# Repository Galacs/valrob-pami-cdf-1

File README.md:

# Carte Pami CDF 1

Pami integrated circuit board with dual silent stepper driver and ToF sensor

## IC List

- ESP32-S3FH4R2 (Main MCU)
- LDL212 (MCU 3v3 LDO)
- BQ77905 (battery protection)
- WS2812B (RGB addressable led)
- MLT-5020 (buzzer)
- VL53L0X (ToF ranging sensor)
- 2x TMC2209 (Silent 3A stepper driver)

## Top preview

## Preview 3d render

## Pictures

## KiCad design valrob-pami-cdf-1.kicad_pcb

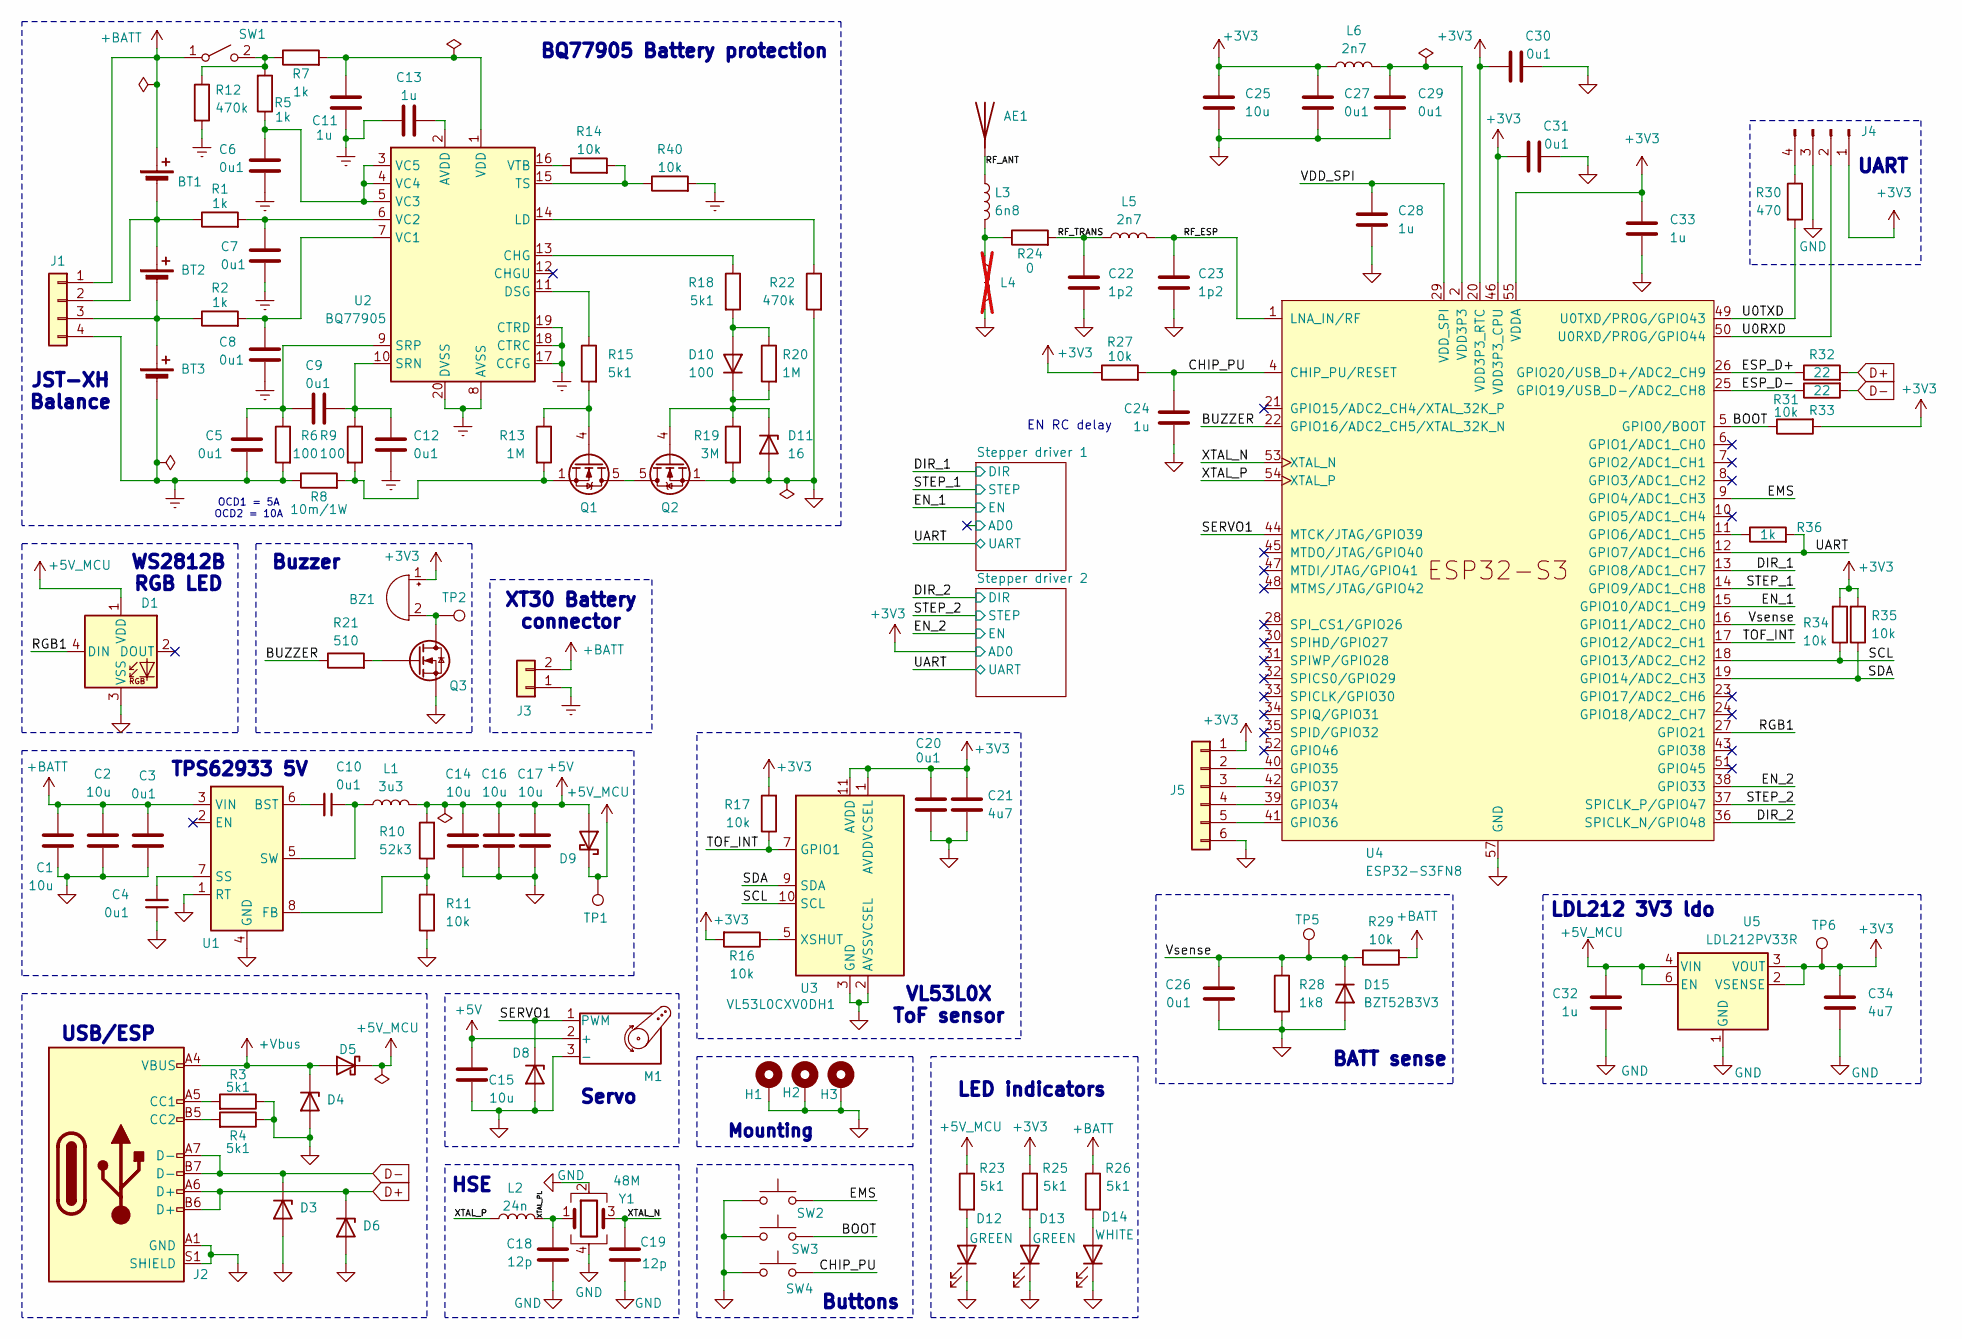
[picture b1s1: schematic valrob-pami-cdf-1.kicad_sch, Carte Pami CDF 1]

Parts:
AE1: Antenna; Johanson_2450AT18x100; Manufacturer Part Number RFANT3216120A5T; JLCPCB Part # C127629
BT1, BT2, BT3: Battery_Cell
BZ1: Buzzer; MagneticBuzzer_Huaneng_MLT-5020; Manufacturer Part Number MLT-5020; JLCPCB Part # C94598
C1, C2, C14, C15, C16, C17: 10u; C_0805_2012Metric; Manufacturer Part Number GRM21BR61H106KE43L; JLCPCB Part # C440198
C3, C4, C5, C6, C7, C8, C9, C10, C12, C20, C26, C27, C29, C30, C31: 0u1; C_0402_1005Metric; Manufacturer Part Number CL05B104KB54PNC; JLCPCB Part # C307331
C11, C13, C24, C28, C32, C33: 1u; C_0402_1005Metric; Manufacturer Part Number CL05A105KA5NQNC; JLCPCB Part # C52923
C18, C19: 12p; C_0402_1005Metric; Manufacturer Part Number 0402CG120J500NT; JLCPCB Part # C1547
C21, C34: 4u7; C_0402_1005Metric; Manufacturer Part Number CL05A475MP5NRNC; JLCPCB Part # C23733
C22, C23: 1p2; C_0402_1005Metric; Manufacturer Part Number GJM1555C1H1R2WB01D; JLCPCB Part # C76899
C25: 10u; C_0402_1005Metric; Manufacturer Part Number CL05A106MQ5NUNC; JLCPCB Part # C15525
D1: WS2812B; LED_WS2812B_PLCC4_5.0x5.0mm_P3.2mm; Manufacturer Part Number WS2812B-V5/W; JLCPCB Part # C2874885
D3, D4, D6, D8: H5VU10U; Diode_DFN1006; Manufacturer Part Number H5VU10U; JLCPCB Part # C22395519
D5, D9: D_Schottky; D_SMA; Manufacturer Part Number SS54; JLCPCB Part # C22452
D10: 100; D_SOD-323; Manufacturer Part Number 1N4148WS; JLCPCB Part # C2128
D11: 16; D_SOD-123; Manufacturer Part Number MMSZ5246B; JLCPCB Part # C19077429
D12, D13: GREEN; LED_0805_2012Metric; Manufacturer Part Number KT-0805G; JLCPCB Part # C2297
D14: WHITE; LED_0603_1608Metric; Manufacturer Part Number KT-0603W; JLCPCB Part # C2290
D15: BZT52B3V3; D_SOD-123; Manufacturer Part Number BZT52B3V3; JLCPCB Part # C19077392
H1, H2, H3: MountingHole_Pad; MountingHole_2.2mm_M2_Pad_Via
J1: Conn_01x04; JST_XH_S4B-XH-A_1x04_P2.50mm_Horizontal
J2: USB_C_Receptacle_USB2.0_14P; USB_C_Receptacle_HRO_TYPE-C-31-M-12; Manufacturer Part Number TYPE-C16PIN; JLCPCB Part # C393939
J3: Conn_01x02; AMASS_XT30PW-M_1x02_P2.50mm_Horizontal; Manufacturer Part Number XT30PW-M30.G.Y; JLCPCB Part # C431092
J4: Conn_01x04_Pin; PinHeader_1x04_P2.54mm_Vertical
J5: Conn_01x06; PinHeader_2x03_P2.54mm_Vertical
L1: 3u3; L_Sunlord_MWSA0402S; Manufacturer Part Number FXL0420-3R3-M; JLCPCB Part # C167207
L2: 24n; L_0402_1005Metric; Manufacturer Part Number LQW15AN24NG00D; JLCPCB Part # C167472
L3: 6n8; L_0402_1005Metric; Manufacturer Part Number LQG15HS6N8J02D; JLCPCB Part # C77110
L4: L; L_0402_1005Metric; not fitted
L5, L6: 2n7; L_0402_1005Metric; Manufacturer Part Number LQG15HS2N7S02D; JLCPCB Part # C77108
M1: Motor_Servo; PinHeader_1x03_P2.54mm_Horizontal
Q1, Q2: Q_NMOS; Vishay_PowerPAK_1212-8_Single; Manufacturer Part Number SIS412DN-T1-GE3; JLCPCB Part # C111309
Q3: Q_NMOS; SOT-323_SC-70; Manufacturer Part Number BSS138W; JLCPCB Part # C28646265
R1, R2, R5, R7, R36: 1k; R_0402_1005Metric; Manufacturer Part Number 0402WGF1001TCE; JLCPCB Part # C11702
R3, R4, R15, R18, R23, R25, R26: 5k1; R_0402_1005Metric; Manufacturer Part Number 0402WGF5101TCE; JLCPCB Part # C25905
R6, R9: 100; R_0402_1005Metric; Manufacturer Part Number 0402WGF1000TCE; JLCPCB Part # C25076
R8: 10m/1W; R_1206_3216Metric; Manufacturer Part Number FMF06FTHR010-LH; JLCPCB Part # C105362
R10: 52k3; R_0402_1005Metric; Manufacturer Part Number 0402WGF5232TCE; JLCPCB Part # C26982
R11, R14, R16, R17, R27, R29, R31, R34, R35, R40: 10k; R_0402_1005Metric; Manufacturer Part Number 0402WGF1002TCE; JLCPCB Part # C25744
R12, R22: 470k; R_0603_1608Metric; Manufacturer Part Number 0603WAF4703T5E; JLCPCB Part # C23178
R13, R20: 1M; R_0402_1005Metric; Manufacturer Part Number 0402WGF1004TCE; JLCPCB Part # C26083
R19: 3M; R_0603_1608Metric; Manufacturer Part Number 0603WAF3004T5E; JLCPCB Part # C23156
R21: 510; R_0402_1005Metric; Manufacturer Part Number 0402WGF5100TCE; JLCPCB Part # C25123
R24: 0; R_0402_1005Metric; Manufacturer Part Number 0402WGF0000TCE; JLCPCB Part # C17168
R28: 1k8; R_0603_1608Metric; Manufacturer Part Number 0603WAF1801T5E; JLCPCB Part # C4177
R30: 470; R_0402_1005Metric; Manufacturer Part Number 0402WGF4700TCE; JLCPCB Part # C25117
R32, R33: 22; R_0402_1005Metric; Manufacturer Part Number 0402WGF220JTCE; JLCPCB Part # C25092
SW1: SW_SPST; PinHeader_1x02_P2.54mm_Vertical
SW2: SW_Push; JST_XH_B2B-XH-A_1x02_P2.50mm_Vertical; Manufacturer Part Number B2B-XH-A(LF)(SN); JLCPCB Part # C158012
SW3, SW4: SW_Push; SW_SPST_TS-1088-xR020; Manufacturer Part Number TS-1088-AR02016; JLCPCB Part # C720477
TP1, TP2, TP5, TP6: TestPoint; TestPoint_Pad_D2.0mm
U1: TPS62933; SOT-583-8; Manufacturer Part Number TPS62933DRLR; JLCPCB Part # C3200405
U2: BQ77905; TSSOP-20_4.4x6.5mm_P0.65mm; Manufacturer Part Number BQ7790509PWR; JLCPCB Part # C2866527
U3: VL53L0CXV0DH1; ST_VL53L1x; Manufacturer Part Number VL53L0CXV0DH/1; JLCPCB Part # C91199
U4: ESP32-S3FN8; QFN-56-1EP_7x7mm_P0.4mm_EP4x4mm_ThermalVias; Manufacturer Part Number ESP32-S3FH4R2; JLCPCB Part # C3013940
U5: LDL212PV33R; DFN-6-1EP_2x2mm_P0.5mm_ST; Manufacturer Part Number LDL212PV33R; JLCPCB Part # C2969892
Y1: 48M; Crystal_SMD_2016-4Pin_2.0x1.6mm; Manufacturer Part Number R940000096; JLCPCB Part # C7206306

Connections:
+3V3: BZ1.1 (+), C20.1, C21.1, C25.1, C27.1, C30.1, C31.1, C33.1, C34.1, J4.1, J5.1, L6.1, R16.2, R17.2, R25.1, R27.1, R31.2, R34.2, R35.2, TP6.1 (1_1), U3.1 (AVDDVCSEL), U3.11 (AVDD), U4.20 (VDD3P3_RTC), U4.46 (VDD3P3_CPU), U4.55 (VDDA), U4.56 (VDDA), U5.2 (VSENSE), U5.3 (VOUT); also elsewhere on the board
+5V: C14.1, C15.1, C16.1, C17.1, D9.2 (A), L1.2, M1.2 (+), R10.2
+5V_MCU: C32.1, D1.1 (VDD), D5.1 (K), D9.1 (K), R23.1, TP1.1 (1_1), U5.4 (VIN), U5.6 (EN)
+BATT: BT1.1 (+), C1.1, C2.1, C3.1, J1.1, J3.2, R26.1, R29.2, SW1.1 (A), U1.3 (VIN); also elsewhere on the board
+Vbus: D4.1 (K), D5.2 (A), J2.A4 (VBUS), J2.A9 (VBUS), J2.B4 (VBUS), J2.B9 (VBUS)
/BOOT: R31.1, SW3.2, U4.5 (GPIO0/BOOT)
/BUZZER: R21.1, U4.22 (GPIO16/ADC2_CH5/XTAL_32K_N)
/CHIP_PU: C24.1, R27.2, SW4.2, U4.4 (CHIP_PU/RESET)
/DIR_1: U4.13 (GPIO8/ADC1_CH7); also elsewhere on the board
/DIR_2: U4.36 (SPICLK_N/GPIO48); also elsewhere on the board
/EMS: SW2.2, U4.9 (GPIO4/ADC1_CH3)
/EN_1: U4.15 (GPIO10/ADC1_CH9); also elsewhere on the board
/EN_2: U4.38 (GPIO33); also elsewhere on the board
/ESP_D+: R32.1, U4.26 (GPIO20/USB_D+/ADC2_CH9)
/ESP_D-: R33.1, U4.25 (GPIO19/USB_D-/ADC2_CH8)
/RF_ANT: AE1.1 (A_1), L3.1
/RF_ESP: C23.1, L5.2, U4.1 (LNA_IN/RF)
/RF_TRANS: C22.1, L5.1, R24.2
/RGB1: D1.4 (DIN), U4.27 (GPIO21)
/SCL: R34.1, U3.10 (SCL), U4.18 (GPIO13/ADC2_CH2)
/SDA: R35.1, U3.9 (SDA), U4.19 (GPIO14/ADC2_CH3)
/SERVO1: D8.1 (K), M1.1 (PWM), U4.44 (MTCK/JTAG/GPIO39)
/STEP_1: U4.14 (GPIO9/ADC1_CH8); also elsewhere on the board
/STEP_2: U4.37 (SPICLK_P/GPIO47); also elsewhere on the board
/TOF_INT: R17.1, U3.7 (GPIO1), U4.17 (GPIO12/ADC2_CH1)
/U0RXD: J4.2, U4.50 (U0RXD/PROG/GPIO44)
/U0TXD: R30.2, U4.49 (U0TXD/PROG/GPIO43)
/UART: R36.2, U4.12 (GPIO7/ADC1_CH6); also elsewhere on the board
/VDD_SPI: C28.1, U4.29 (VDD_SPI)
/Vsense: C26.1, D15.1 (K), R28.1, R29.1, TP5.1 (1_1), U4.16 (GPIO11/ADC2_CH0)
/XTAL_N: C19.1, U4.53 (XTAL_N), Y1.3
/XTAL_P: L2.1, U4.54 (XTAL_P)
/XTAL_PL: C18.2, L2.2, Y1.1
BGND: BT3.2 (-), C5.2, C6.2, C7.2, C8.2, C11.1, C12.2, C13.2, J1.4, J3.1, R6.2, R8.1, R12.2, R40.2, U2.8 (AVSS), U2.17 (CCFG), U2.18 (CTRC), U2.19 (CTRD), U2.20 (DVSS)
D+: D6.1 (K), J2.A6 (D+), J2.B6 (D+), R32.2
D-: D3.1 (K), J2.A7 (D-), J2.B7 (D-), R33.2
GND: C1.2, C2.2, C3.2, C4.1, C14.2, C15.2, C16.2, C17.2, C18.1, C19.2, C20.2, C21.2, C22.2, C23.2, C24.2, C25.2, C26.2, C27.2, C28.2, C29.2, C30.2, C31.2, C32.2, C33.2, C34.2, D1.3 (VSS), D3.2 (A), D4.2 (A), D6.2 (A), D8.2 (A), D11.2 (A), D12.1 (K), D13.1 (K), D14.1 (K), D15.2 (A), H1.1 (1_1), H2.1 (1_1), H3.1 (1_1), J2.A1 (GND), J2.A12 (GND), J2.B1 (GND), J2.B12 (GND), J2.S1 (SHIELD), J4.3, J5.6, L4.2, M1.3 (-), Q2.1 (S), Q2.2 (S), Q2.3 (S), Q3.2 (S), R3.1, R4.1, R11.1, R19.2, R22.2, R28.2, SW2.1, SW3.1, SW4.1, U1.1 (RT), U1.4 (GND), U3.2 (AVSSVCSEL), U3.3 (GND), U3.4 (GND), U3.6 (GND), U3.12 (GND), U4.57 (GND), U5.1 (GND), Y1.2, Y1.4; also elsewhere on the board
unnamed: BZ1.2 (-), Q3.3 (D), TP2.1 (1_1)
unnamed: D10.2 (A), R18.2, R20.1
unnamed: D10.1 (K), D11.1 (K), Q2.4 (G), R19.1, R20.2
unnamed: D12.2 (A), R23.2
unnamed: D13.2 (A), R25.2
unnamed: D14.2 (A), R26.2
unnamed: BT1.2 (-), BT2.1 (+), J1.2, R1.1
unnamed: BT2.2 (-), BT3.1 (+), J1.3, R2.1
unnamed: J2.A5 (CC1), R3.2
unnamed: J2.B5 (CC2), R4.2
unnamed: J4.4, R30.1
unnamed: J5.2, U4.40 (GPIO35)
unnamed: J5.3, U4.42 (GPIO37)
unnamed: J5.4, U4.39 (GPIO34)
unnamed: J5.5, U4.41 (GPIO36)
unnamed: L3.2, L4.1, R24.1
unnamed: Q1.5 (D), Q2.5 (D)
unnamed: Q1.4 (G), R13.1, R15.2
unnamed: Q1.1 (S), Q1.2 (S), Q1.3 (S), R8.2, R9.2, R13.2
unnamed: Q3.1 (G), R21.2
unnamed: R5.2, R7.1, R12.1, SW1.2 (B)
unnamed: C10.2, U1.6 (BST)
unnamed: R10.1, R11.2, U1.8 (FB)
unnamed: C4.2, U1.7 (SS)
unnamed: C10.1, L1.1, U1.5 (SW)
unnamed: C13.1, U2.2 (AVDD)
unnamed: R18.1, U2.13 (CHG)
unnamed: R15.1, U2.11 (DSG)
unnamed: R22.1, U2.14 (LD)
unnamed: C9.1, C12.1, R9.1, U2.10 (SRN)
unnamed: C5.1, C9.2, R6.1, U2.9 (SRP)
unnamed: R14.2, R40.1, U2.15 (TS)
unnamed: C8.1, R2.2, U2.7 (VC1)
unnamed: C7.1, R1.2, U2.6 (VC2)
unnamed: C6.1, R5.1, U2.3 (VC5), U2.4 (VC4), U2.5 (VC3)
unnamed: C11.2, R7.2, U2.1 (VDD)
unnamed: R14.1, U2.16 (VTB)
unnamed: R16.1, U3.5 (XSHUT)
unnamed: R36.1, U4.11 (GPIO6/ADC1_CH5)
VDD3P3: C29.1, L6.2, U4.2 (VDD3P3), U4.3 (VDD3P3)

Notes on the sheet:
UART
Buttons
LDL212 3V3 ldo
OCD1 = 5A OCD2 = 10A
JST-XH Balance
BQ77905 Battery protection
Servo
VL53L0X ToF sensor
EN RC delay
BATT sense
WS2812B RGB LED
LED indicators
Buzzer
TPS62933 5V
HSE
USB/ESP
XT30 Battery connector
Mounting

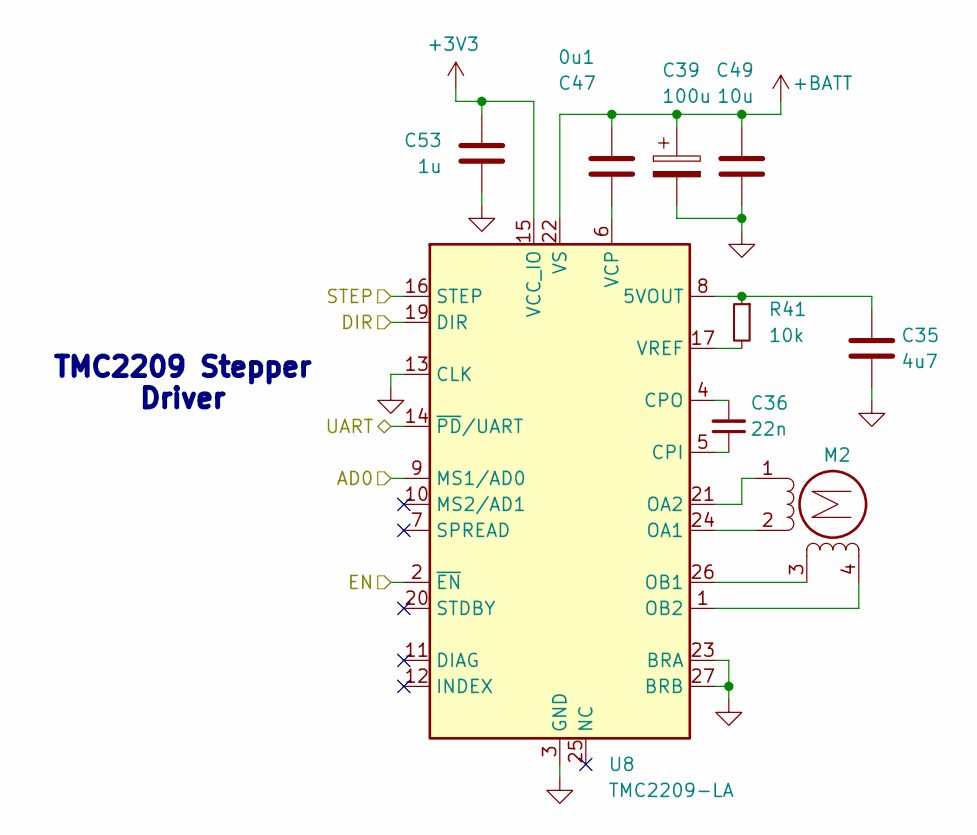
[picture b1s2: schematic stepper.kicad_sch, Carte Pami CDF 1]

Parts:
C35: 4u7; C_0402_1005Metric; Manufacturer Part Number CL05A475MP5NRNC; JLCPCB Part # C23733
C36: 22n; C_0402_1005Metric; Manufacturer Part Number 0402B223K500NT; JLCPCB Part # C1532
C39: 100u; CP_Elec_6.3x7.7; Manufacturer Part Number EEEFTH101XAP; JLCPCB Part # C165974
C47: 0u1; C_0402_1005Metric; Manufacturer Part Number CL05B104KB54PNC; JLCPCB Part # C307331
C49: 10u; C_0805_2012Metric; Manufacturer Part Number GRM21BR61H106KE43L; JLCPCB Part # C440198
C53: 1u; C_0402_1005Metric; Manufacturer Part Number CL05A105KA5NQNC; JLCPCB Part # C52923
M2: Stepper_Motor_bipolar; JST_XH_S4B-XH-A_1x04_P2.50mm_Horizontal
R41: 10k; R_0402_1005Metric; Manufacturer Part Number 0402WGF1002TCE; JLCPCB Part # C25744
U8: TMC2209-LA; VQFN-28-1EP_5x5mm_P0.5mm_EP3.7x3.7mm_ThermalVias; Manufacturer Part Number TMC2209-LA-T; JLCPCB Part # C2150710

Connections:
+3V3: C53.1, U8.15 (VCC_IO); also elsewhere on the board
+BATT: C39.1, C47.1, C49.1, U8.22 (VS), U8.28 (VS); also elsewhere on the board
/DIR_1: U8.19 (DIR); also elsewhere on the board
/EN_1: U8.2 (~EN); also elsewhere on the board
/STEP_1: U8.16 (STEP); also elsewhere on the board
/Stepper driver 1/AD0: U8.9 (MS1/AD0)
/UART: U8.14 (~PD/UART); also elsewhere on the board
GND: C35.2, C39.2, C49.2, C53.2, U8.3 (GND), U8.13 (CLK), U8.18 (GND), U8.23 (BRA), U8.27 (BRB), U8.29 (GND); also elsewhere on the board
unnamed: M2.1 (-_1), U8.21 (OA2)
unnamed: C35.1, R41.1, U8.8 (5VOUT)
unnamed: C36.1, U8.5 (CPI)
unnamed: C36.2, U8.4 (CPO)
unnamed: M2.2, U8.24 (OA1)
unnamed: M2.3, U8.26 (OB1)
unnamed: M2.4, U8.1 (OB2)
unnamed: C47.2, U8.6 (VCP)
unnamed: R41.2, U8.17 (VREF)

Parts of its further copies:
C37: 4u7; C_0402_1005Metric; Manufacturer Part Number CL05A475MP5NRNC; JLCPCB Part # C23733
C42: 22n; C_0402_1005Metric; Manufacturer Part Number 0402B223K500NT; JLCPCB Part # C1532
C45: 100u; CP_Elec_6.3x7.7; Manufacturer Part Number EEEFTH101XAP; JLCPCB Part # C165974
C48: 0u1; C_0402_1005Metric; Manufacturer Part Number CL05B104KB54PNC; JLCPCB Part # C307331
C50: 10u; C_0805_2012Metric; Manufacturer Part Number GRM21BR61H106KE43L; JLCPCB Part # C440198
C54: 1u; C_0402_1005Metric; Manufacturer Part Number CL05A105KA5NQNC; JLCPCB Part # C52923
M3: Stepper_Motor_bipolar; JST_XH_S4B-XH-A_1x04_P2.50mm_Horizontal
R42: 10k; R_0402_1005Metric; Manufacturer Part Number 0402WGF1002TCE; JLCPCB Part # C25744
U9: TMC2209-LA; VQFN-28-1EP_5x5mm_P0.5mm_EP3.7x3.7mm_ThermalVias; Manufacturer Part Number TMC2209-LA-T; JLCPCB Part # C2150710

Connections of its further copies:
+3V3: C54.1, U9.9 (MS1/AD0), U9.15 (VCC_IO); also elsewhere on the board
+BATT: C45.1, C48.1, C50.1, U9.22 (VS), U9.28 (VS); also elsewhere on the board
/DIR_2: U9.19 (DIR); also elsewhere on the board
/EN_2: U9.2 (~EN); also elsewhere on the board
/STEP_2: U9.16 (STEP); also elsewhere on the board
/UART: U9.14 (~PD/UART); also elsewhere on the board
GND: C37.2, C45.2, C50.2, C54.2, U9.3 (GND), U9.13 (CLK), U9.18 (GND), U9.23 (BRA), U9.27 (BRB), U9.29 (GND); also elsewhere on the board
unnamed: M3.1 (-_1), U9.21 (OA2)
unnamed: C37.1, R42.1, U9.8 (5VOUT)
unnamed: C42.1, U9.5 (CPI)
unnamed: C42.2, U9.4 (CPO)
unnamed: M3.2, U9.24 (OA1)
unnamed: M3.3, U9.26 (OB1)
unnamed: M3.4, U9.1 (OB2)
unnamed: C48.2, U9.6 (VCP)
unnamed: R42.2, U9.17 (VREF)

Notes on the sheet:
TMC2209 Stepper Driver

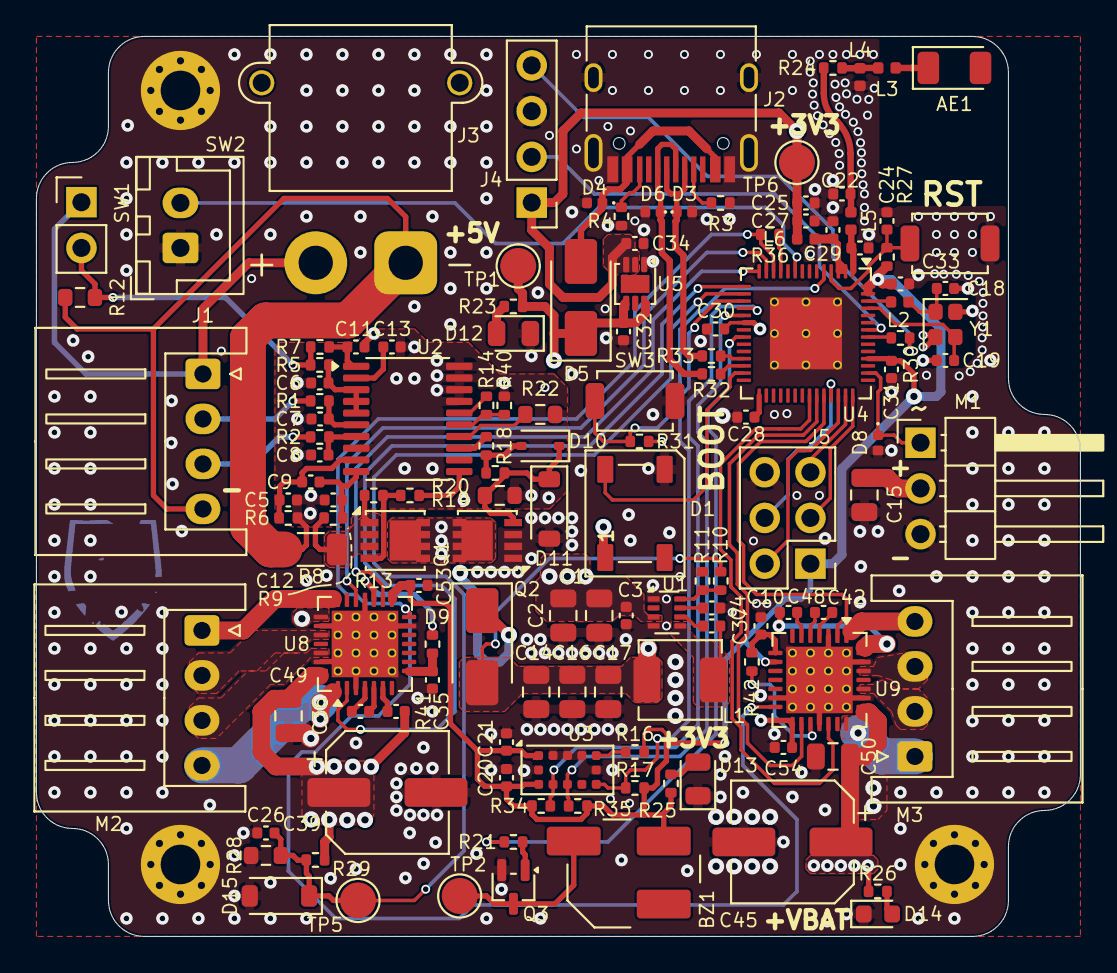
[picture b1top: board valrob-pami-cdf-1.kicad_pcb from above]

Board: 4 copper layers, 58.0 x 50.0 mm, 136 parts (0 on the bottom side), 95 nets.

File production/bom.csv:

Designator,Footprint,Quantity,Value,LCSC Part #
AE1,Johanson_2450AT18x100,1,Antenna,C127629
BZ1,MagneticBuzzer_Huaneng_MLT-5020,1,Buzzer,C94598
"C1, C14, C16, C17, C2",0805,5,10u,C440198
"C10, C12, C20, C26, C27, C29, C3, C30, C31, C4, C5, C6, C7, C8, C9",0402,15,0u1,C307331
"C11, C13, C24, C28, C32, C33, C38, C40, C44, C46",0402,10,1u,C52923
"C18, C19",0402,2,12p,C1547
"C21, C34",0402,2,4u7,C23733
"C22, C23",0402,2,1p2,C76899
C25,0402,1,10u,C15525
"C35, C36, C41, C42",0402,4,22n,C1532
"C37, C43",0402,2,10n,C15195
"C39, C45",CP_Elec_6.3x7.7,2,100u,C165974
D1,LED_WS2812B_PLCC4_5.0x5.0mm_P3.2mm,1,WS2812B,C2874885
D10,D_SOD-323,1,100,C2128
D11,D_SOD-123,1,16,C19077429
"D12, D13",0805,2,GREEN,C2297
D14,0603,1,WHITE,C2290
D15,D_SOD-123,1,BZT52B3V3,C19077392
"D3, D4, D6, D8",Diode_DFN1006,4,H5VU10U,C22395519
"D5, D9",D_SMA,2,D_Schottky,C22452
J2,USB_C_Receptacle_HRO_TYPE-C-31-M-12,1,USB_C_Receptacle_USB2.0_14P,C393939
J3,AMASS_XT30PW-M_1x02_P2.50mm_Horizontal,1,Conn_01x02,C431092
J5,PinHeader_2x03_P2.54mm_Vertical,1,Conn_01x06,
L1,L_Sunlord_MWSA0402S,1,3u3,C167207
L2,0402,1,24n,C167472
L3,0402,1,6n8,C77110
"L5, L6",0402,2,2n7,C77108
"Q1, Q2",Vishay_PowerPAK_1212-8_Single,2,Q_NMOS,C111309
Q3,SOT-323_SC-70,1,Q_NMOS,C28646265
"R1, R2, R37, R39, R5, R7",0402,6,1k,C11702
R10,0402,1,52k3,C26982
"R11, R14, R16, R17, R27, R29, R31, R34, R35, R36, R38, R40",0402,12,10k,C25744
"R12, R22",0603,2,470k,C23178
"R13, R20",0402,2,1M,C26083
"R15, R18, R23, R25, R26, R3, R4",0402,7,5k1,C25905
R19,0603,1,3M,C23156
R21,0402,1,510,C25123
R24,0402,1,0,C17168
R28,0603,1,1k8,C4177
R30,0402,1,470,C25117
"R32, R33",0402,2,22,C25092
"R6, R9",0402,2,100,C25076
R8,1206,1,10m/1W,C105362
SW2,JST_XH_B2B-XH-A_1x02_P2.50mm_Vertical,1,SW_Push,C158012
"SW3, SW4",SW_SPST_TS-1088-xR020,2,SW_Push,C720477
U1,SOT-583-8,1,TPS62933,C3200405
U2,TSSOP-20_4.4x6.5mm_P0.65mm,1,BQ77905,C2866527
U3,ST_VL53L1x,1,VL53L0CXV0DH1,C91199
U4,QFN-56-1EP_7x7mm_P0.4mm_EP4x4mm_ThermalVias,1,ESP32-S3FN8,C3013940
U5,DFN-6-1EP_2x2mm_P0.5mm_ST,1,LDL212PV33R,C2969892
"U6, U7",Texas_RGE0024B_VQFN-24-1EP_4x4mm_P0.5mm_EP2.5x2.5mm_ThermalVias,2,DRV8424RGER,C1518725
Y1,Crystal_SMD_2016-4Pin_2.0x1.6mm,1,48M,C7206306

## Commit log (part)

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2026-02-16 schem: import esp32-s3 circuit from mhadb-main-board
2026-02-16 schem: import HSE crystal
2026-02-16 schem: import usbc connector
2026-02-16 schem: import LDL212 3V3 ldo
2026-02-16 schem: add BOOT and CHIP_PU buttons*
2026-02-16 schem: add 3x WS2812B RGB LEDs
2026-02-16 schem: add servo connector
2026-02-16 schem: import BQ77905 Battery protection
2026-02-16 schem: import buzzer
2026-02-16 schem: add XT30 battery connector
2026-02-16 pcb: add indicator leds
2026-02-16 schem: add BQ77905 enable pull down resistor
2026-02-16 schem: import DRV8424 stepper driver and reorganize
2026-02-16 schem: add placeholder TPS56A37 5V smps
2026-02-16 schem: import BATT sense from valrob-alim
2026-02-18 schem: add missing rgb leds ground symbol
2026-02-20 schem: set stepper driver microstepping and decay config
2026-02-20 schem: change stepper driver connector
2026-02-20 schem: fix stepper hierachical sheets
2026-02-21 schem: change buck converter to TPS62933 5V
2026-02-21 schem: add VL53L0x tof sensor
2026-02-22 schem: add EMS button
2026-02-22 schem: add mounting holes
2026-02-22 schem: connecto all gpios to mcu
2026-02-22 schem: add test points
2026-02-22 schem: reannotate
2026-02-22 schem: run and fix ERC
2026-02-22 schem: import net classes from mhadb-main-board
2026-02-22 schem: fix BOM
2026-02-22 schem: add title
2026-02-22 schem: change rgb led 5v rail
2026-02-22 pcb: import 4 layer stackup and constraints
2026-02-22 pcb: import components and add missing 3d models
2026-02-22 pcb: add stepper layout
2026-02-22 pcb: add usbc layout
2026-02-22 pcb: add initial smps layout
2026-02-22 pcb: add bms layout
2026-02-22 pcb: add missing xt30 3d model
2026-02-22 pcb: refine layout and add board outline
2026-02-22 schem: update connectors to horizontal footprints
2026-02-22 schem: update servo connector to horizontal
2026-02-22 pcb: change connectors layout
2026-02-22 schem: add 6 spare gpio header
2026-02-22 pcb: refine board outline
2026-02-22 pcb: add gnd planes
2026-02-22 pcb: add gnd vias
2026-02-22 pcb: add drill/place origin
2026-02-22 schem/pcb: reorganize programmable gpios
2026-02-22 pcb: add rf routing
2026-02-22 pcb: add crystal routing
2026-02-22 pcb: add usb routing
2026-02-22 pcb: add uart routing
2026-02-22 pcb: add servo connector routing
2026-02-22 pcb: add smps routing
2026-02-22 pcb: add bms routing
2026-02-22 pcb: add buzzer routing
2026-02-22 pcb: add local stepper drivers routing
2026-02-22 pcb: add right stepper driver routing
2026-02-22 pcb: fix bms BGND pour
2026-02-22 pcb: add tof sensor routing
2026-02-22 pcb: add missing stepper drv fault 2 connection
2026-02-22 pcb: add left stepper driver routing
2026-02-22 pcb: add RGB led routing
2026-02-22 pcb: add spare gpio routing
2026-02-22 pcb: fix right stepper drv gnd island
2026-02-22 pcb: add EMS routing
2026-02-22 pcb: add +BATT routing
2026-02-22 pcb: add +3V3 pwr routing
2026-02-22 pcb: add 5V pwr routing
2026-02-22 pcb: add +VBUS pwr routing
2026-02-22 pcb: add BOOT routing
2026-02-22 pcb: add VDD_SPI routing
2026-02-22 pcb: add status leds routing
2026-02-22 pcb: fix missing gnd connections
2026-02-22 schem: add no connects
2026-02-22 pcb: clean up trace appearance
2026-02-23 schem: fix L exclude from BOM
2026-02-23 pcb: add stitching vias
2026-02-23 pcb: run and fix DRC
2026-02-23 pcb: remove unused internal pads
2026-02-23 pcb(silk): clean up reference designators
2026-02-23 pcb(silk): add user txt
2026-02-23 pcb(silk): add more bling
2026-02-23 pcb: add title
2026-02-23 generate production files
2026-03-10 pcb: add step export settings
2026-04-12 update to kicad 10
2026-04-12 schem: add TMC2209 Stepper driver
2026-04-13 schem: connect new stepper driver to mcu
2026-04-13 schem: add ordering info to BOM
2026-04-13 pcb: import new driver from schem
2026-04-13 pcb: add missing 3d models
2026-04-13 pcb: add new drivers layout
2026-04-13 pcb: add right stepper drv routing
2026-04-13 pcb: add left stepper drv routing
2026-04-13 schem/pcb: fix stepper driver vcc_io voltage
2026-04-13 rev02
2026-04-13 regenerate production files
